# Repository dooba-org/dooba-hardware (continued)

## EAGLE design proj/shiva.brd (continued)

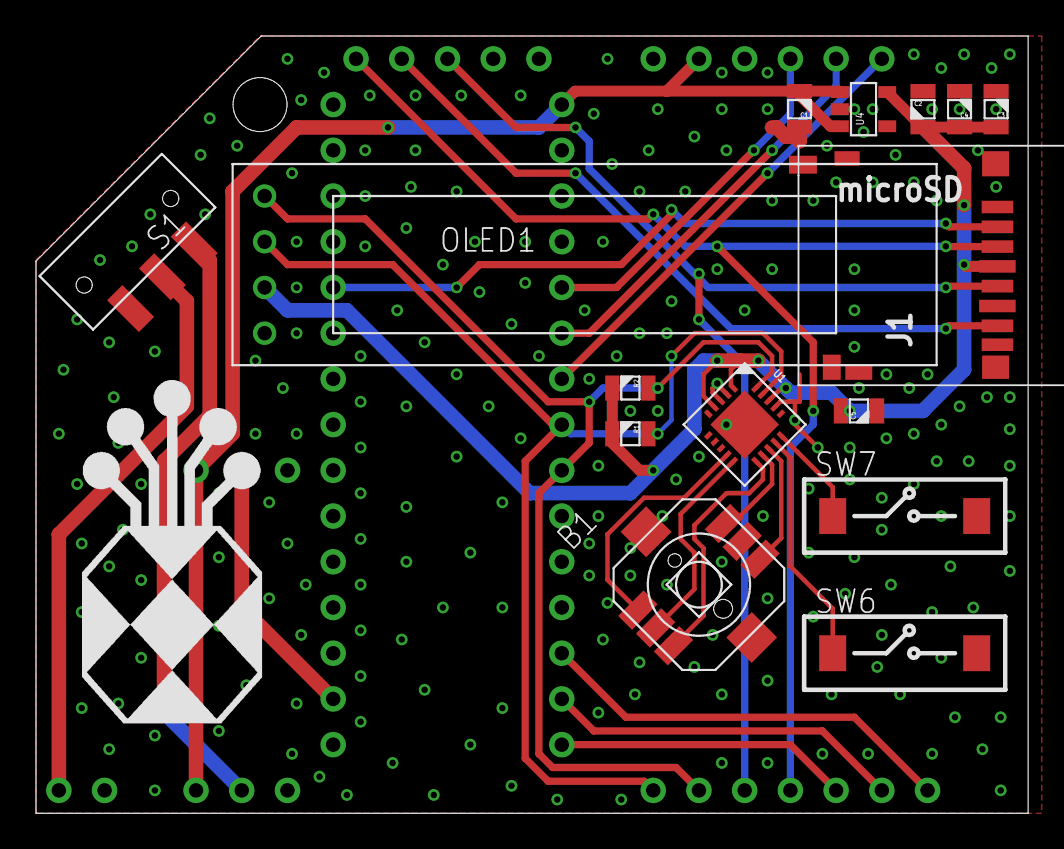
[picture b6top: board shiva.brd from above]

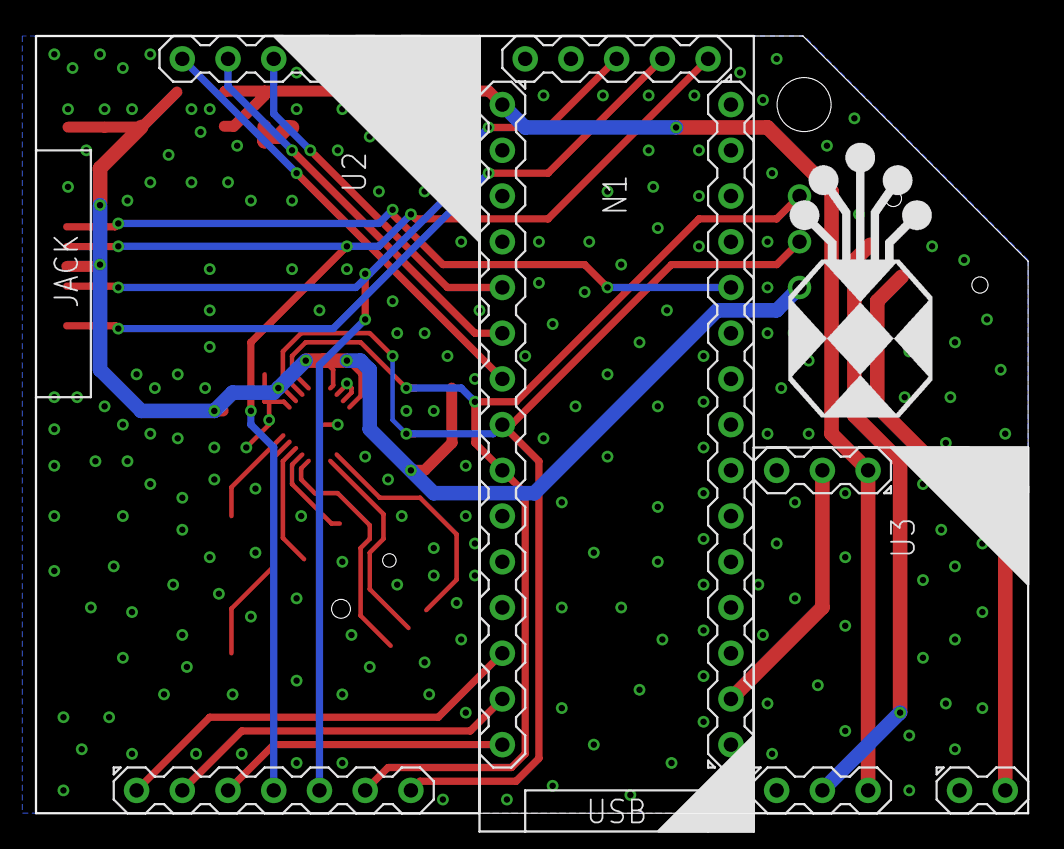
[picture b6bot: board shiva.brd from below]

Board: 2 copper layers, 55.1 x 43.2 mm, 18 parts (3 on the bottom side), 25 nets.

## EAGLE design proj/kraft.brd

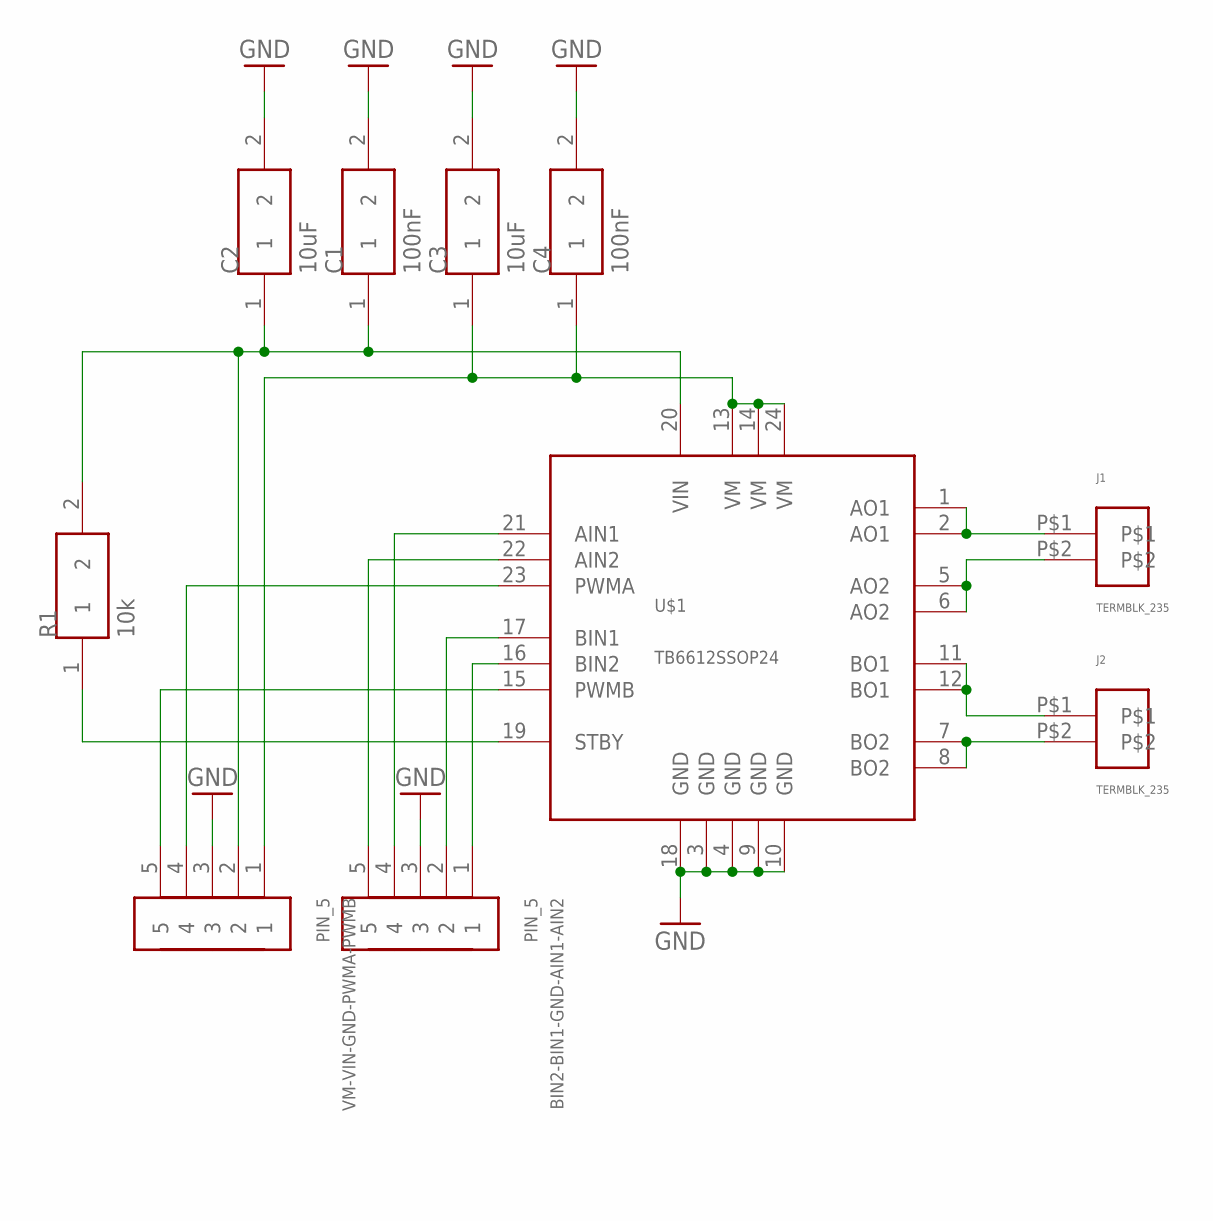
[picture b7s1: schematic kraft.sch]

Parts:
BIN2-BIN1-GND-AIN1-AIN2: PIN_5
C1, C4: 100nF; 0805
C2, C3: 10uF; 0805
J1, J2: TERMBLK_235; TERMBLK_35_2
R1: 10k; 0805
U$1: TB6612SSOP24; SSOP24
VM-VIN-GND-PWMA-PWMB: PIN_5

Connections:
GND: BIN2-BIN1-GND-AIN1-AIN2.3, C1.2, C2.2, C3.2, C4.2, U$1.3 (GND), U$1.4 (GND), U$1.9 (GND), U$1.10 (GND), U$1.18 (GND), VM-VIN-GND-PWMA-PWMB.3
unnamed: C1.1, C2.1, R1.2, U$1.20 (VIN), VM-VIN-GND-PWMA-PWMB.2
unnamed: C3.1, C4.1, U$1.13 (VM), U$1.14 (VM), U$1.24 (VM), VM-VIN-GND-PWMA-PWMB.1
unnamed: U$1.23 (PWMA), VM-VIN-GND-PWMA-PWMB.4
unnamed: U$1.15 (PWMB), VM-VIN-GND-PWMA-PWMB.5
unnamed: BIN2-BIN1-GND-AIN1-AIN2.4, U$1.21 (AIN1)
unnamed: BIN2-BIN1-GND-AIN1-AIN2.5, U$1.22 (AIN2)
unnamed: BIN2-BIN1-GND-AIN1-AIN2.2, U$1.17 (BIN1)
unnamed: BIN2-BIN1-GND-AIN1-AIN2.1, U$1.16 (BIN2)
unnamed: R1.1, U$1.19 (STBY)
unnamed: J1.P$1, U$1.1 (AO1), U$1.2 (AO1)
unnamed: J1.P$2, U$1.5 (AO2), U$1.6 (AO2)
unnamed: J2.P$1, U$1.11 (BO1), U$1.12 (BO1)
unnamed: J2.P$2, U$1.7 (BO2), U$1.8 (BO2)

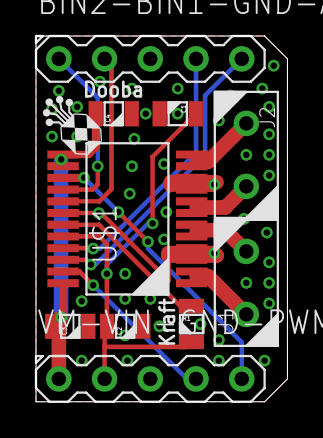
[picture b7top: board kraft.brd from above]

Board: 2 copper layers, 14.0 x 20.3 mm, 10 parts (0 on the bottom side), 14 nets.

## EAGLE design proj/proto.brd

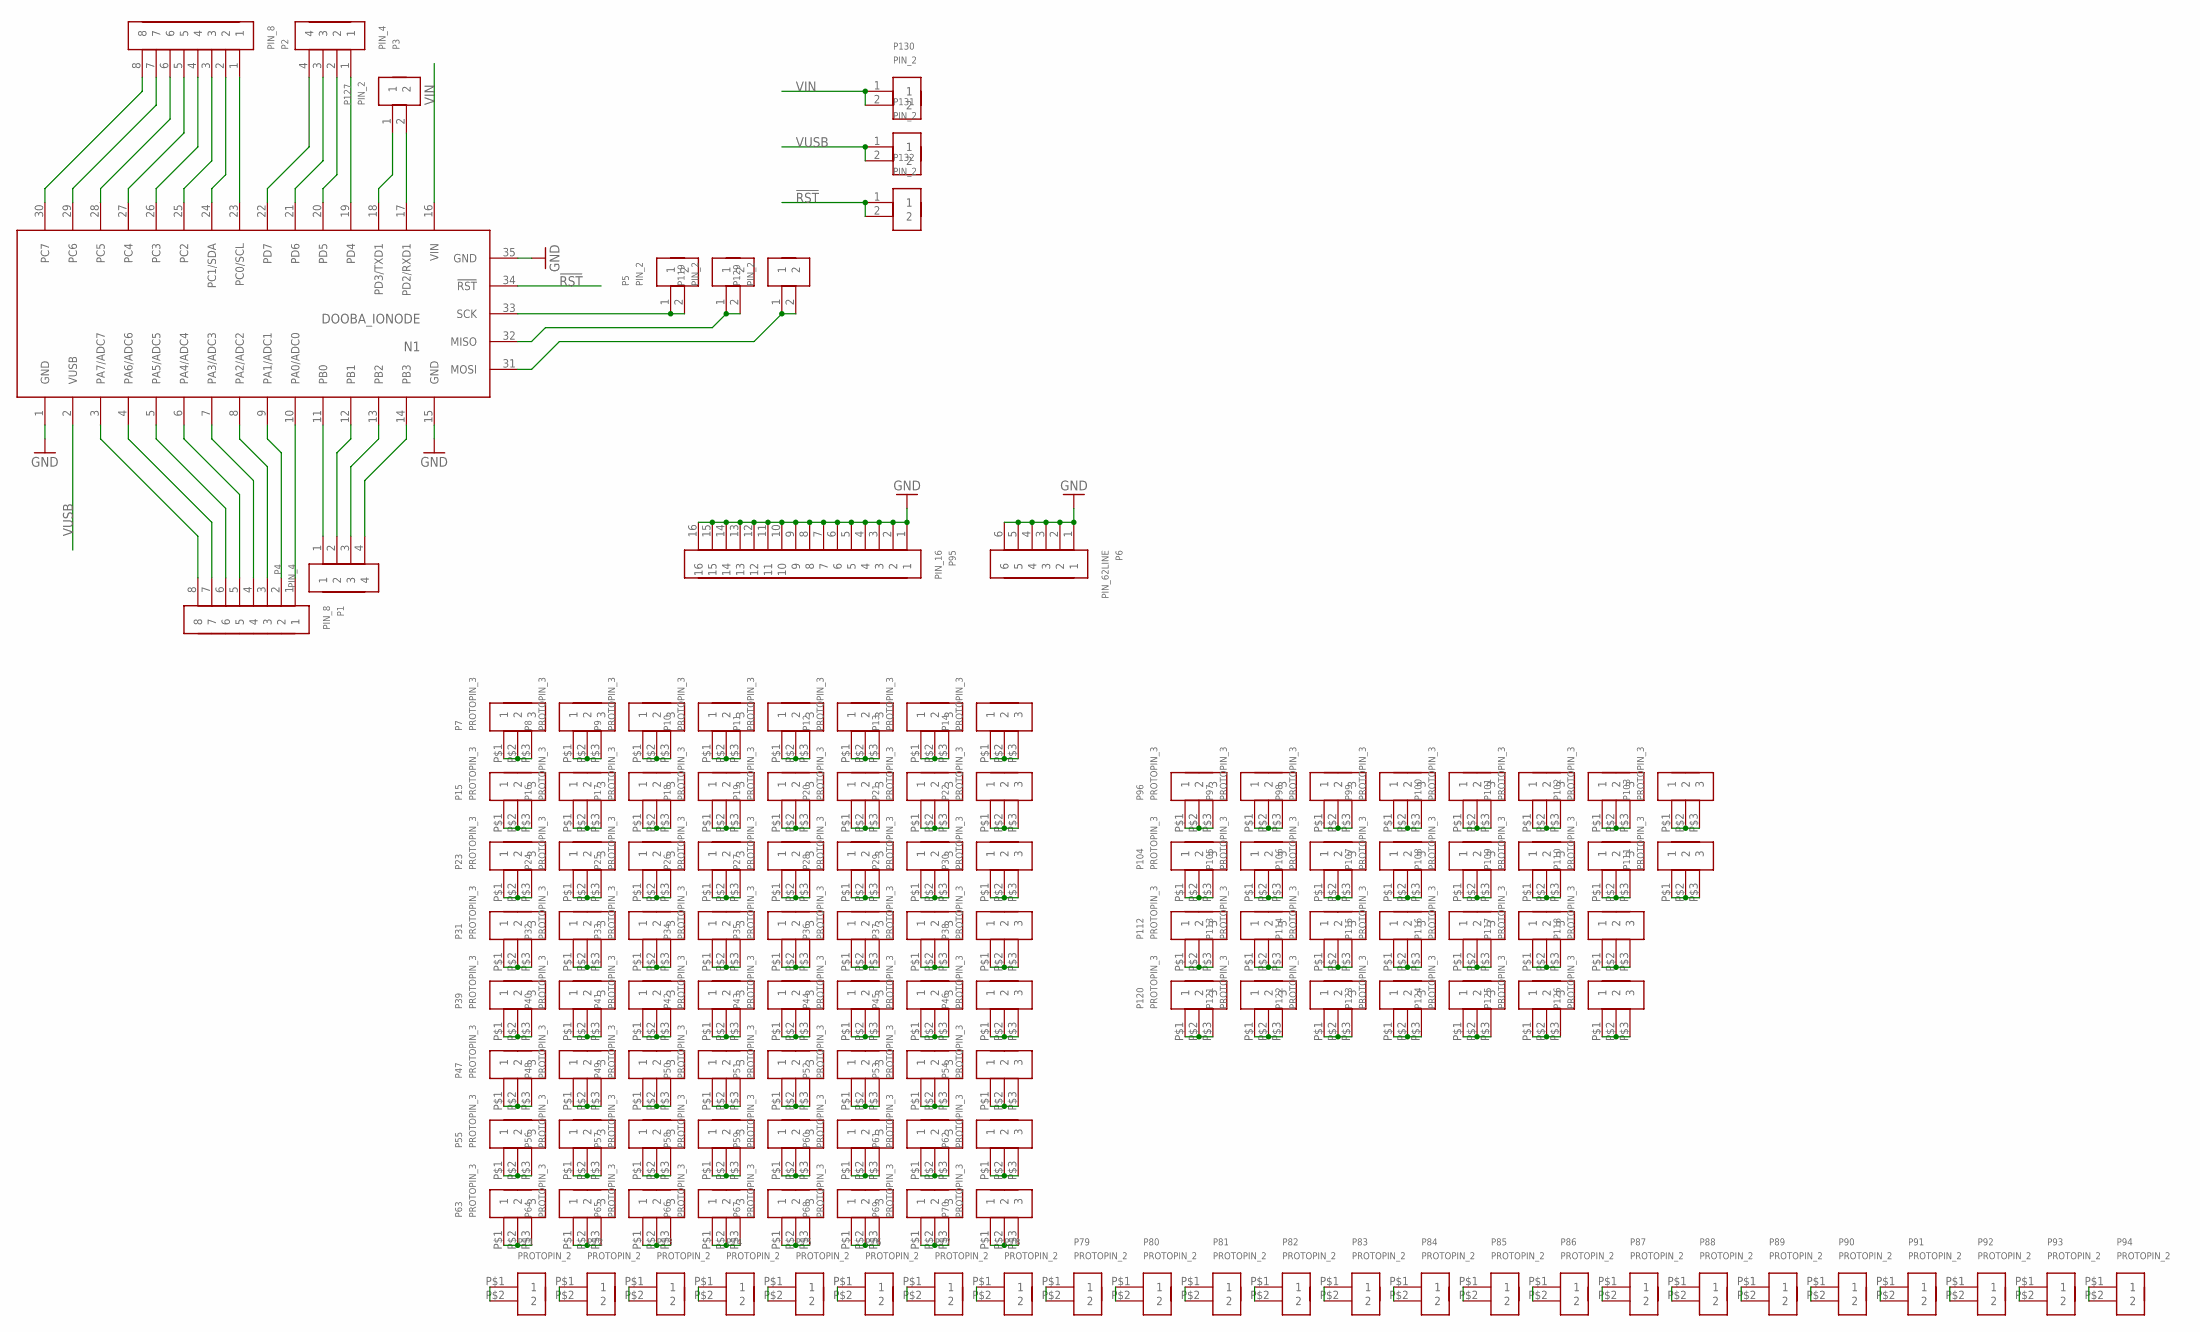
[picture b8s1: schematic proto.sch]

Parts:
N1: DOOBA_IONODE
P1, P2: PIN_8
P3, P4: PIN_4
P5, P119, P127, P129, P130, P131, P132: PIN_2
P6: PIN_62LINE; PIN_3X2
P7, P8, P9, P10, P11, P12, P13, P14, P15, P16, P17, P18, P19, P20, P21, P22, P23, P24, P25, P26, P27, P28, P29, P30, P31, P32, P33, P34, P35, P36, P37, P38, P39, P40, P41, P42, P43, P44, P45, P46, P47, P48, P49, P50, P51, P52, P53, P54, P55, P56, P57, P58, P59, P60, P61, P62, P63, P64, P65, P66, P67, P68, P69, P70, P96, P97, P98, P99, P100, P101, P102, P103, P104, P105, P106, P107, P108, P109, P110, P111, P112, P113, P114, P115, P116, P117, P118, P120, P121, P122, P123, P124, P125, P126: PROTOPIN_3
P71, P72, P73, P74, P75, P76, P77, P78, P79, P80, P81, P82, P83, P84, P85, P86, P87, P88, P89, P90, P91, P92, P93, P94: PROTOPIN_2
P95: PIN_16

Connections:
!RST: N1.34 (!RST), P132.1, P132.2
GND: N1.1 (GND), N1.15 (GND), N1.35 (GND), P6.1, P6.2, P6.3, P6.4, P6.5, P6.6, P95.1, P95.2, P95.3, P95.4, P95.5, P95.6, P95.7, P95.8, P95.9, P95.10, P95.11, P95.12, P95.13, P95.14, P95.15, P95.16
unnamed: N1.23 (PC0/SCL), P2.1
unnamed: N1.24 (PC1/SDA), P2.2
unnamed: N1.25 (PC2), P2.3
unnamed: N1.26 (PC3), P2.4
unnamed: N1.27 (PC4), P2.5
unnamed: N1.28 (PC5), P2.6
unnamed: N1.29 (PC6), P2.7
unnamed: N1.30 (PC7), P2.8
unnamed: N1.19 (PD4), P3.1
unnamed: N1.20 (PD5), P3.2
unnamed: N1.21 (PD6), P3.3
unnamed: N1.22 (PD7), P3.4
unnamed: N1.10 (PA0/ADC0), P1.1
unnamed: N1.9 (PA1/ADC1), P1.2
unnamed: N1.8 (PA2/ADC2), P1.3
unnamed: N1.7 (PA3/ADC3), P1.4
unnamed: N1.6 (PA4/ADC4), P1.5
unnamed: N1.5 (PA5/ADC5), P1.6
unnamed: N1.4 (PA6/ADC6), P1.7
unnamed: N1.3 (PA7/ADC7), P1.8
unnamed: N1.11 (PB0), P4.1
unnamed: N1.12 (PB1), P4.2
unnamed: N1.13 (PB2), P4.3
unnamed: N1.14 (PB3), P4.4
unnamed: N1.33 (SCK), P5.1, P5.2
unnamed: N1.32 (MISO), P119.1, P119.2
unnamed: N1.31 (MOSI), P129.1, P129.2
unnamed: P7.P$1 (1), P7.P$2 (2), P7.P$3 (3)
unnamed: P8.P$1 (1), P8.P$2 (2), P8.P$3 (3)
unnamed: P9.P$1 (1), P9.P$2 (2), P9.P$3 (3)
unnamed: P10.P$1 (1), P10.P$2 (2), P10.P$3 (3)
unnamed: P11.P$1 (1), P11.P$2 (2), P11.P$3 (3)
unnamed: P12.P$1 (1), P12.P$2 (2), P12.P$3 (3)
unnamed: P13.P$1 (1), P13.P$2 (2), P13.P$3 (3)
unnamed: P14.P$1 (1), P14.P$2 (2), P14.P$3 (3)
unnamed: P15.P$1 (1), P15.P$2 (2), P15.P$3 (3)
unnamed: P16.P$1 (1), P16.P$2 (2), P16.P$3 (3)
unnamed: P17.P$1 (1), P17.P$2 (2), P17.P$3 (3)
unnamed: P18.P$1 (1), P18.P$2 (2), P18.P$3 (3)
unnamed: P19.P$1 (1), P19.P$2 (2), P19.P$3 (3)
unnamed: P20.P$1 (1), P20.P$2 (2), P20.P$3 (3)
unnamed: P21.P$1 (1), P21.P$2 (2), P21.P$3 (3)
unnamed: P22.P$1 (1), P22.P$2 (2), P22.P$3 (3)
unnamed: P23.P$1 (1), P23.P$2 (2), P23.P$3 (3)
unnamed: P24.P$1 (1), P24.P$2 (2), P24.P$3 (3)
unnamed: P25.P$1 (1), P25.P$2 (2), P25.P$3 (3)
unnamed: P26.P$1 (1), P26.P$2 (2), P26.P$3 (3)
unnamed: P27.P$1 (1), P27.P$2 (2), P27.P$3 (3)
unnamed: P28.P$1 (1), P28.P$2 (2), P28.P$3 (3)
unnamed: P29.P$1 (1), P29.P$2 (2), P29.P$3 (3)
unnamed: P30.P$1 (1), P30.P$2 (2), P30.P$3 (3)
unnamed: P31.P$1 (1), P31.P$2 (2), P31.P$3 (3)
unnamed: P32.P$1 (1), P32.P$2 (2), P32.P$3 (3)
unnamed: P33.P$1 (1), P33.P$2 (2), P33.P$3 (3)
unnamed: P34.P$1 (1), P34.P$2 (2), P34.P$3 (3)
unnamed: P35.P$1 (1), P35.P$2 (2), P35.P$3 (3)
unnamed: P36.P$1 (1), P36.P$2 (2), P36.P$3 (3)
unnamed: P37.P$1 (1), P37.P$2 (2), P37.P$3 (3)
unnamed: P38.P$1 (1), P38.P$2 (2), P38.P$3 (3)
unnamed: P39.P$1 (1), P39.P$2 (2), P39.P$3 (3)
unnamed: P40.P$1 (1), P40.P$2 (2), P40.P$3 (3)
unnamed: P41.P$1 (1), P41.P$2 (2), P41.P$3 (3)
unnamed: P42.P$1 (1), P42.P$2 (2), P42.P$3 (3)
unnamed: P43.P$1 (1), P43.P$2 (2), P43.P$3 (3)
unnamed: P44.P$1 (1), P44.P$2 (2), P44.P$3 (3)
unnamed: P45.P$1 (1), P45.P$2 (2), P45.P$3 (3)
unnamed: P46.P$1 (1), P46.P$2 (2), P46.P$3 (3)
unnamed: P47.P$1 (1), P47.P$2 (2), P47.P$3 (3)
unnamed: P48.P$1 (1), P48.P$2 (2), P48.P$3 (3)
unnamed: P49.P$1 (1), P49.P$2 (2), P49.P$3 (3)
unnamed: P50.P$1 (1), P50.P$2 (2), P50.P$3 (3)
unnamed: P51.P$1 (1), P51.P$2 (2), P51.P$3 (3)
unnamed: P52.P$1 (1), P52.P$2 (2), P52.P$3 (3)
unnamed: P53.P$1 (1), P53.P$2 (2), P53.P$3 (3)
unnamed: P54.P$1 (1), P54.P$2 (2), P54.P$3 (3)
unnamed: P55.P$1 (1), P55.P$2 (2), P55.P$3 (3)
unnamed: P56.P$1 (1), P56.P$2 (2), P56.P$3 (3)
unnamed: P57.P$1 (1), P57.P$2 (2), P57.P$3 (3)
unnamed: P58.P$1 (1), P58.P$2 (2), P58.P$3 (3)
unnamed: P59.P$1 (1), P59.P$2 (2), P59.P$3 (3)
unnamed: P60.P$1 (1), P60.P$2 (2), P60.P$3 (3)
unnamed: P61.P$1 (1), P61.P$2 (2), P61.P$3 (3)
unnamed: P62.P$1 (1), P62.P$2 (2), P62.P$3 (3)
unnamed: P63.P$1 (1), P63.P$2 (2), P63.P$3 (3)
unnamed: P64.P$1 (1), P64.P$2 (2), P64.P$3 (3)
unnamed: P65.P$1 (1), P65.P$2 (2), P65.P$3 (3)
unnamed: P66.P$1 (1), P66.P$2 (2), P66.P$3 (3)
unnamed: P67.P$1 (1), P67.P$2 (2), P67.P$3 (3)
unnamed: P68.P$1 (1), P68.P$2 (2), P68.P$3 (3)
unnamed: P69.P$1 (1), P69.P$2 (2), P69.P$3 (3)
unnamed: P70.P$1 (1), P70.P$2 (2), P70.P$3 (3)
unnamed: P71.P$1 (1), P71.P$2 (2)
unnamed: P72.P$1 (1), P72.P$2 (2)
unnamed: P73.P$1 (1), P73.P$2 (2)
unnamed: P74.P$1 (1), P74.P$2 (2)
unnamed: P75.P$1 (1), P75.P$2 (2)
unnamed: P76.P$1 (1), P76.P$2 (2)
unnamed: P77.P$1 (1), P77.P$2 (2)
unnamed: P78.P$1 (1), P78.P$2 (2)
unnamed: P79.P$1 (1), P79.P$2 (2)
unnamed: P80.P$1 (1), P80.P$2 (2)
unnamed: P81.P$1 (1), P81.P$2 (2)
unnamed: P82.P$1 (1), P82.P$2 (2)
unnamed: P83.P$1 (1), P83.P$2 (2)
unnamed: P84.P$1 (1), P84.P$2 (2)
unnamed: P85.P$1 (1), P85.P$2 (2)
unnamed: P86.P$1 (1), P86.P$2 (2)
unnamed: P87.P$1 (1), P87.P$2 (2)
unnamed: P88.P$1 (1), P88.P$2 (2)
unnamed: P89.P$1 (1), P89.P$2 (2)
unnamed: P90.P$1 (1), P90.P$2 (2)
unnamed: P91.P$1 (1), P91.P$2 (2)
unnamed: P92.P$1 (1), P92.P$2 (2)
unnamed: P93.P$1 (1), P93.P$2 (2)
unnamed: P94.P$1 (1), P94.P$2 (2)
unnamed: P96.P$1 (1), P96.P$2 (2), P96.P$3 (3)
unnamed: P97.P$1 (1), P97.P$2 (2), P97.P$3 (3)
unnamed: P98.P$1 (1), P98.P$2 (2), P98.P$3 (3)
unnamed: P99.P$1 (1), P99.P$2 (2), P99.P$3 (3)
unnamed: P100.P$1 (1), P100.P$2 (2), P100.P$3 (3)
unnamed: P101.P$1 (1), P101.P$2 (2), P101.P$3 (3)
unnamed: P102.P$1 (1), P102.P$2 (2), P102.P$3 (3)
unnamed: P103.P$1 (1), P103.P$2 (2), P103.P$3 (3)
unnamed: P104.P$1 (1), P104.P$2 (2), P104.P$3 (3)
unnamed: P105.P$1 (1), P105.P$2 (2), P105.P$3 (3)
unnamed: P106.P$1 (1), P106.P$2 (2), P106.P$3 (3)
unnamed: P107.P$1 (1), P107.P$2 (2), P107.P$3 (3)
unnamed: P108.P$1 (1), P108.P$2 (2), P108.P$3 (3)
unnamed: P109.P$1 (1), P109.P$2 (2), P109.P$3 (3)
unnamed: P110.P$1 (1), P110.P$2 (2), P110.P$3 (3)
unnamed: P111.P$1 (1), P111.P$2 (2), P111.P$3 (3)
unnamed: P112.P$1 (1), P112.P$2 (2), P112.P$3 (3)
unnamed: P113.P$1 (1), P113.P$2 (2), P113.P$3 (3)
unnamed: P114.P$1 (1), P114.P$2 (2), P114.P$3 (3)
unnamed: P115.P$1 (1), P115.P$2 (2), P115.P$3 (3)
unnamed: P116.P$1 (1), P116.P$2 (2), P116.P$3 (3)
unnamed: P117.P$1 (1), P117.P$2 (2), P117.P$3 (3)
unnamed: P118.P$1 (1), P118.P$2 (2), P118.P$3 (3)
unnamed: N1.17 (PD2/RXD1), P127.2
unnamed: P120.P$1 (1), P120.P$2 (2), P120.P$3 (3)
unnamed: P121.P$1 (1), P121.P$2 (2), P121.P$3 (3)
unnamed: P122.P$1 (1), P122.P$2 (2), P122.P$3 (3)
unnamed: P123.P$1 (1), P123.P$2 (2), P123.P$3 (3)
unnamed: P124.P$1 (1), P124.P$2 (2), P124.P$3 (3)
unnamed: P125.P$1 (1), P125.P$2 (2), P125.P$3 (3)
unnamed: P126.P$1 (1), P126.P$2 (2), P126.P$3 (3)
unnamed: N1.18 (PD3/TXD1), P127.1
VIN: N1.16 (VIN), P130.1, P130.2
VUSB: N1.2 (VUSB), P131.1, P131.2

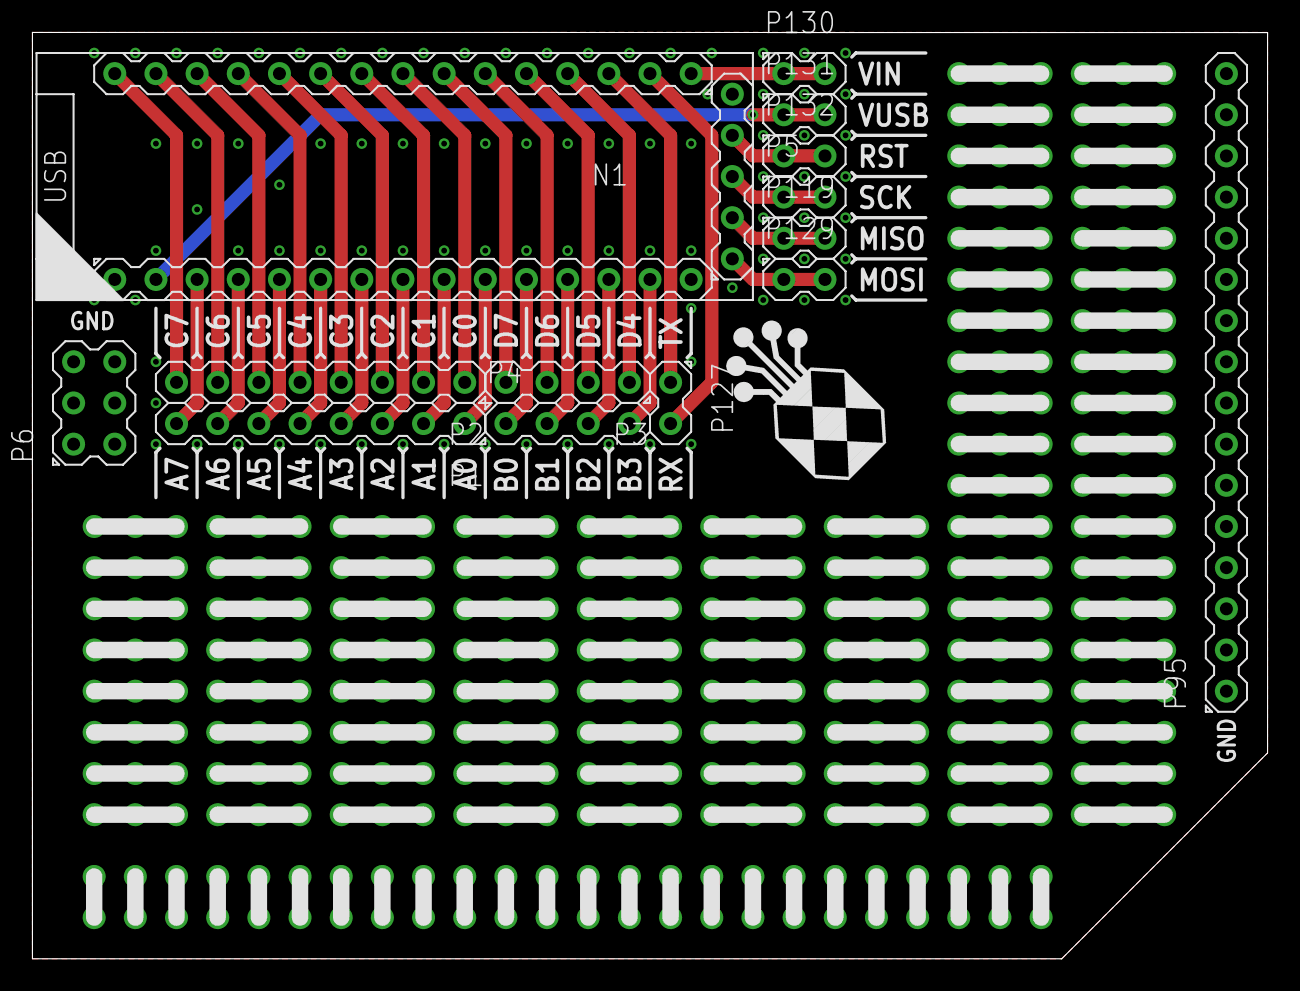
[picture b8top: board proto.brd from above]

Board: 2 copper layers, 76.2 x 57.1 mm, 132 parts (0 on the bottom side), 151 nets.

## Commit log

2016-10-15 Started adding parts to Dooba Eagle Library: - ST Micro STM32F030 - ST Micro STM32F071 - Spansion / Cypress S25FL128S / S25FL256S
2016-10-15 Connected STM32F071
2016-10-15 Added Microchip's ENC28J60 to Dooba Eagle Lib
2016-10-15 Added ARJC02-111008B Ethernet MagJack Connector
2016-10-15 Added some SMD res/cap/led/xtal
2016-10-16 Started designing Dooba dsy01 board :D
2016-10-16 Added AS6C1608 2048Kb SRAM to DSY01
2016-10-17 Further designed DSY01
2016-10-22 Added Workers to DSY01 Board Added some parts to Dooba Eagle Lib (MIC550X, Pins)
2016-10-23 Added more Pin headers to Dooba Eagle Lib Added RST signal and extension header to DSY01
2016-10-26 Added CAM and DRU files for Eagle Further routed DSY01 board
2016-10-28 Further designed DSY01 Board & Schematic
2016-11-05 Further routed DSY01
2016-11-06 Further routed DSY01 board
2016-11-07 Routed power supply on DSY01 board
2016-11-08 Finished routing DSY01 Added LEDs on DSY01
2016-11-09 Started decorating DSY01
2016-11-10 Added more decorations to DSY01
2016-11-11 Finished decorating (?) DSY01
2016-11-11 Added package-oshpark board packaging script
2016-11-11 Added Gerber files to clean script
2016-11-11 fixed clean script
2016-11-11 Added board zip to clean script
2016-11-11 Added missing decoration to DSY01 (LED + RES)
2016-11-11 Refactored oshpark package script to include dirtypcbs
2016-11-12 Provided DSY01 Dock Template (Schematic + Board) Started designing DSD01-BSTA Basic Station Dock (Schematic done, layout done)
2016-11-13 Routed DSD01-BSTA
2016-11-15 Completed DSY01 & DSD01-BSTA boards
2016-12-18 Added ioNode Board
2016-12-26 Started ioNode SunBoard (4x20 LCD + USB UART + LiPo)
2017-01-12 Started shiva mp3 player board
2017-01-12 Added some parts to Eagle Library Further designed Shiva MP3 Player schematic
2017-01-12 Added OLED Display to Shiva MP3 Player Started adding button interface
2017-01-13 Further designed Shiva MP3 Player Schematic Added MCP23008 I2C I/O Expander to Eagle Library
2017-01-13 Finished designing Shiva MP3 Player Schematic
2017-01-13 Added some activity LEDs to Shiva MP3 Player Schematic
2017-01-15 Added BOM Tools Completed Shiva MP3 Player Board
2017-01-26 Fixed Stereo jack footprint Designed and routed Aecho mp3 player board
2017-01-27 Fixed ioNode Board (Labels on QFN Thermal pads might not be a good idea...) Fixed CAM file
2017-01-28 Fixed Eagle Package Script
2017-01-28 Redesigned ioNode using ATMEGA1284P, replaced esp8266 with ft232rq usb/serial
2017-01-29 Started designing Shiva mp3 player (new version)
2017-01-31 Finished Shiva board
2017-02-21 Fixed STA013 Device in Eagle Library Fixed Aecho Board to use updated STA013 Fixed ioNode Schematic (74125 buffers for USB UART had their !OE tied to VCC...)
2017-02-21 Fixed Silk error on ioNode
2017-03-12 Cleaned up repository
2017-03-12 Fixed gitignore
2017-03-12 Removed Clean Script Fixed tree Fixed package script
2017-03-12 Reorganized repo
2017-03-12 Added notice
2017-04-11 Improved reference designators on ionode
2017-04-21 Added DRU file for ZhongFeng PCBA Added 0402 footprint Added SMD Jumper footprint Added SMD Jumper to ioNode for VIN - VUSB Upgraded most 0805 parts on ioNode to 0402 Added USART1 TX/RX breakout on i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
2017-04-22 Updated ioNode part in Eagle Library Integrated changes to ioNode part in Shiva board
2017-05-13 Routed stickie board Started designing Tako ethernet module Added ENC28J60 28QFN to Eagle Library
2017-05-13 Exposed SPI interface and reset (+gnd) on ioNode footprint (eagle lib)
2017-05-13 @open #9 @open #4 @close #4 Exposed STA013 BIT_EN line in Aecho module
2017-05-13 Updated Aecho eagle footprint to match new version (BIT_EN exposed) @open #10 @close #10
2017-05-17 Started designing Tako schematic & board @open #11
2017-05-17 Added License
2017-05-17 Updated License
2017-05-21 Added Solder Jumper to Nomad module to select charge current (open = 500mA / closed = 100mA) @open #13 @close #13
2017-05-21 Started re-designing Shiva MP3 schematic & board for hardware SPI Also, made it smaller :) @open #7
2017-05-21 Completed new Shiva board using SPI for MicroSD and Aecho Improved some QFN parts in the Eagle Library Added ref layer to Nomad for ZFPCBA @close #7
2017-05-21 Updated stickie board to use SPI for MicroSD @close #8
2017-05-21 Completed transition to hardware SPI! @close #9
2017-05-23 Completed Tako Module
2017-05-23 @close #11
2017-05-29 Fixed Buttons on Shiva MP3 board (buttons were too close to OLED)
2017-05-31 Completed Kraft & Proto boards
2017-06-20 Completed Kraft Board
2017-06-30 Updated Shiva board to use smaller oled (128x32) and joystick instead of directional buttons Added Fiddle UI Board
2017-07-21 Started designing Funk machine
2017-09-10 Moved 0.91 OLED footprint to docu layer Updated Fiddle schematic & board to include MicroSD and Wifi (esp8266) :D
2017-10-07 tootoot
2017-10-20 Completed mobile phone (untitled) schematic Started routing mobile phone board
2017-10-21 Added Z3OC Vibration Motor to Eagle Library Added Vibrator to mobile phone schematic
2017-10-22 Further routed mobile phone board
2017-10-23 Found a name for the mobile phone: 'Trill'
2017-10-24 Further routed Trill mobile phone board
2017-10-24 Completed Trill mobile phone board
2017-10-25 Added 2 LEDs (PWM-able) to Trill Mobile Phone
2017-10-25 Started routing "slim" version of Trill mobile phone
2017-10-25 Fixed SIM5300EA footprint in library (was missing restrict layer) Completed routing "slim" version of Trill mobile phone - so much awesome.
2017-10-25 Fixed drill sizes in Trill board
2017-10-25 Added missing label on STA013 xtal resistor (1M) in Trill Slim board
2017-10-25 Fixed branding artwork on Trill Slim board
2017-10-26 added some plcc & pdip parts
2017-10-26 Added some parts to eagle library Started drawing up schematic for Rizon Z80 SBC
2017-10-27 Added 74374 to library Further designed Rizon Z80 SBC
2017-10-29 Started designing main board for Rizon Z80 computer
2017-10-30 Cleaned up repo Added raccoon artwork to Trill board
2017-10-30 Further designed Rizon board
2017-10-31 Attempts at designing Rizon board
2017-11-01 Redesigning Rizon board
2017-11-02 Rizon board routing
2017-11-02 Completed Rizon main board (CPU + RAM + ROM) Added Rizon footprint and device to library
2017-11-03 Started designing Rizon I/O board schematic
2017-11-03 Further designed Rizon I/O module schematic
2017-11-05 Routed Rizon I/O board
2017-11-07 Started SMD version of Rizon Computer Cleaned up library
2017-11-07 Started routing SMD version of Rizon board
2017-11-08 Added missing signal net (TIMER_OUT -> INT_TIMER) in Rizon I/O board Further routed SMD version of Rizon computer
2017-11-08 Rizon SMD routing work
2017-11-09 Added breakouts to Rizon SMD
2017-11-10 Rizon SMD routing
2017-11-11 Completed Rizon SMD board
2017-11-13 Updated lib
2017-11-13 Added OLED RESET line on Trill board
2017-11-26 Fixed Trill board (Jack connector & GSM_PWR_KEY)
2017-12-26 Added 3d files
2018-01-02 Added parts to lib
2018-01-19 Cleaned up Trill Case
2018-02-11 Added Battery & SIM covers for Trill Case
2018-02-19 Started added AAA Battery Box
2018-02-20 Added Blender 3D Dooba Logo & Started designing carrying case for batteries (6xAAA)
2018-02-24 Fixed AAA Battery Box
2018-03-20 Added 3D Model of Fiddle Case
